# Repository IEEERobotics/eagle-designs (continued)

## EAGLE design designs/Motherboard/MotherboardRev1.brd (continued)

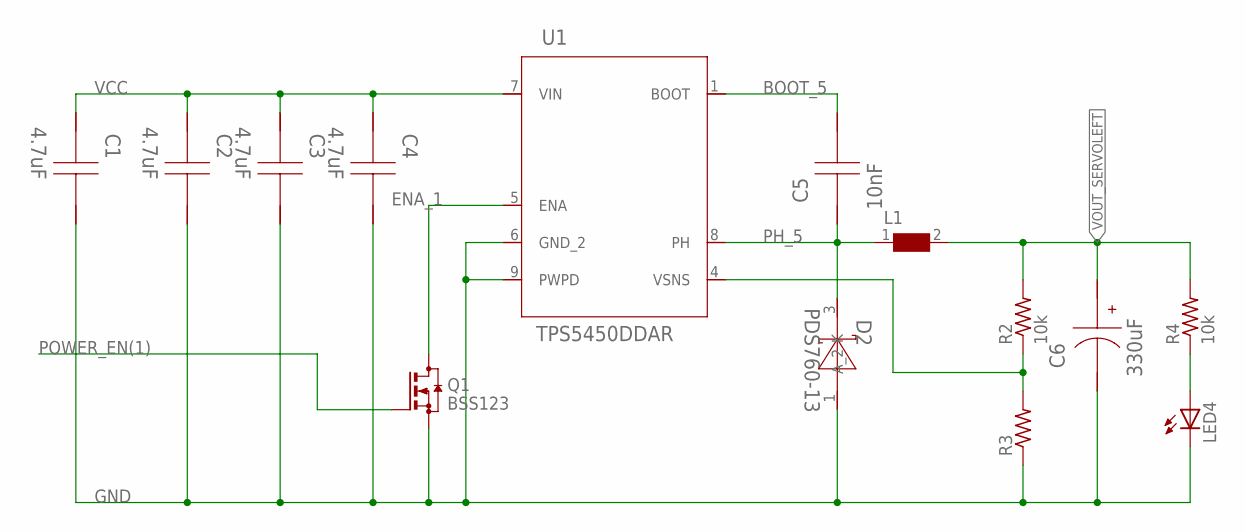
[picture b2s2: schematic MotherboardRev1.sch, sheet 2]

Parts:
C1, C2, C3, C4: 4.7uF; 1206
C5: 10nF; 0805
C6: 330uF; SM_RADIAL_10AMM
D2: PDS760-13; POWERDI5
L1: WE-HCC-7443331000_1090; WE-HCC_1090
LED4: LEDSML1206; SML1206
Q1: BSS123; SOT23
R2, R4: 10k; R1206
R3: R-US_R1206; R1206
U1: TPS5450DDAR; R-PDSO-G8

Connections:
BOOT_5: C5.1, U1.1 (BOOT); also elsewhere on the board
ENA_1: Q1.3 (D), U1.5 (ENA)
GND: C1.1, C2.1, C3.1, C4.1, C6.2 (-), D2.1 (A_2), LED4.C, Q1.2 (S), R3.1, U1.6 (GND_2), U1.9 (PWPD); also elsewhere on the board
unnamed: LED4.A, R4.1
PH_5: C5.2, D2.3 (K), L1.1, U1.8 (PH); also elsewhere on the board
POWER_EN(1): Q1.1 (G)
VCC: C1.2, C2.2, C3.2, C4.2, U1.7 (VIN); also elsewhere on the board
VOUT_SERVOLEFT: C6.1 (+), L1.2, R2.2, R4.2; also elsewhere on the board
VSNS_5: R2.1, R3.2, U1.4 (VSNS)

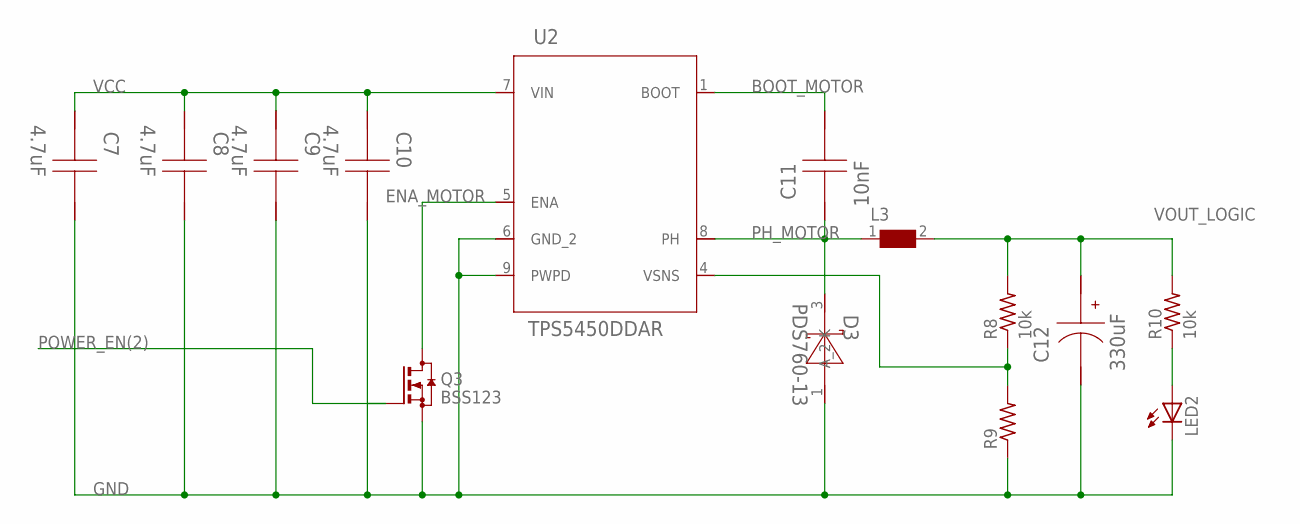
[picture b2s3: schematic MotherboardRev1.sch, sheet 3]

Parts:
C7, C8, C9, C10: 4.7uF; 1206
C11: 10nF; 0805
C12: 330uF; SM_RADIAL_10AMM
D3: PDS760-13; POWERDI5
L3: WE-HCC-7443331000_1090; WE-HCC_1090
LED2: LEDSML1206; SML1206
Q3: BSS123; SOT23
R8, R10: 10k; R1206
R9: R-US_R1206; R1206
U2: TPS5450DDAR; R-PDSO-G8

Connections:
BOOT_MOTOR: C11.1, U2.1 (BOOT); also elsewhere on the board
ENA_MOTOR: Q3.3 (D), U2.5 (ENA); also elsewhere on the board
GND: C7.1, C8.1, C9.1, C10.1, C12.2 (-), D3.1 (A_2), LED2.C, Q3.2 (S), R9.1, U2.6 (GND_2), U2.9 (PWPD); also elsewhere on the board
unnamed: LED2.A, R10.1
PH_MOTOR: C11.2, D3.3 (K), L3.1, U2.8 (PH); also elsewhere on the board
POWER_EN(2): Q3.1 (G)
VCC: C7.2, C8.2, C9.2, C10.2, U2.7 (VIN); also elsewhere on the board
VOUT_LOGIC: C12.1 (+), L3.2, R8.2, R10.2
VSNS1_MOTOR: R8.1, R9.2, U2.4 (VSNS)

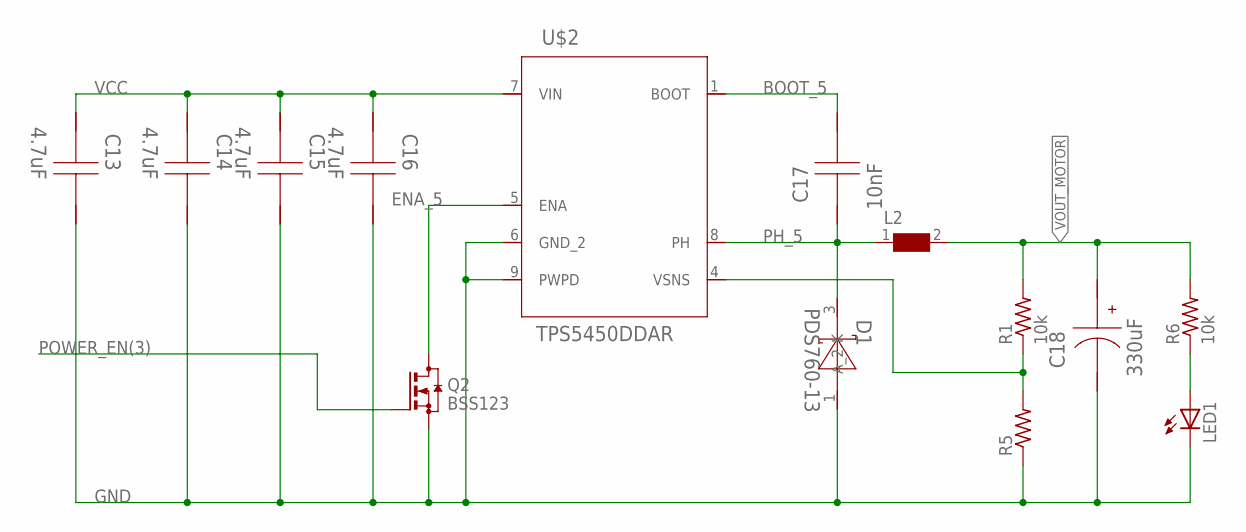
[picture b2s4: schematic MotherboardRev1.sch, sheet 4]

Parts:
C13, C14, C15, C16: 4.7uF; 1206
C17: 10nF; 0805
C18: 330uF; SM_RADIAL_10AMM
D1: PDS760-13; POWERDI5
L2: WE-HCC-7443331000_1090; WE-HCC_1090
LED1: LEDSML1206; SML1206
Q2: BSS123; SOT23
R1, R6: 10k; R1206
R5: R-US_R1206; R1206
U$2: TPS5450DDAR; R-PDSO-G8

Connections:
BOOT_5: C17.1, U$2.1 (BOOT); also elsewhere on the board
ENA_5: Q2.3 (D), U$2.5 (ENA)
GND: C13.1, C14.1, C15.1, C16.1, C18.2 (-), D1.1 (A_2), LED1.C, Q2.2 (S), R5.1, U$2.6 (GND_2), U$2.9 (PWPD); also elsewhere on the board
unnamed: LED1.A, R6.1
PH_5: C17.2, D1.3 (K), L2.1, U$2.8 (PH); also elsewhere on the board
POWER_EN(3): Q2.1 (G)
VCC: C13.2, C14.2, C15.2, C16.2, U$2.7 (VIN); also elsewhere on the board
VOUT_MOTOR: C18.1 (+), L2.2, R1.2, R6.2; also elsewhere on the board
VSNS_1: R1.1, R5.2, U$2.4 (VSNS)

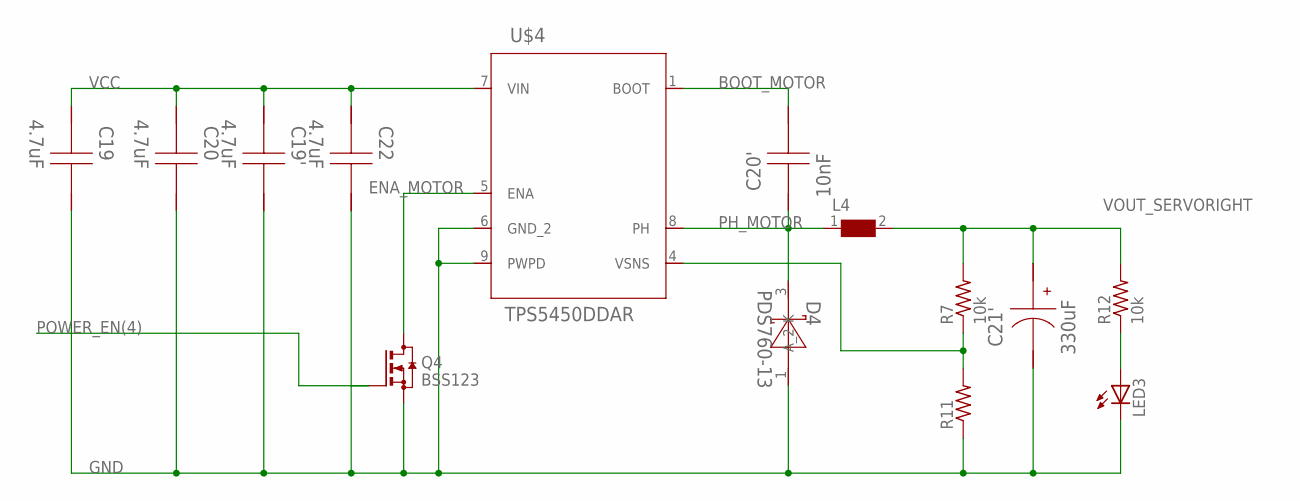
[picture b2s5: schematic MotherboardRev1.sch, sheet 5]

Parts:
C19, C19', C20, C22: 4.7uF; 1206
C20': 10nF; 0805
C21': 330uF; SM_RADIAL_10AMM
D4: PDS760-13; POWERDI5
L4: WE-HCC-7443331000_1090; WE-HCC_1090
LED3: LEDSML1206; SML1206
Q4: BSS123; SOT23
R7, R12: 10k; R1206
R11: R-US_R1206; R1206
U$4: TPS5450DDAR; R-PDSO-G8

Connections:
BOOT_MOTOR: C20'.1, U$4.1 (BOOT); also elsewhere on the board
ENA_MOTOR: Q4.3 (D), U$4.5 (ENA); also elsewhere on the board
GND: C19.1, C19'.1, C20.1, C21'.2 (-), C22.1, D4.1 (A_2), LED3.C, Q4.2 (S), R11.1, U$4.6 (GND_2), U$4.9 (PWPD); also elsewhere on the board
unnamed: LED3.A, R12.1
PH_MOTOR: C20'.2, D4.3 (K), L4.1, U$4.8 (PH); also elsewhere on the board
POWER_EN(4): Q4.1 (G)
VCC: C19.2, C19'.2, C20.2, C22.2, U$4.7 (VIN); also elsewhere on the board
VOUT_SERVORIGHT: C21'.1 (+), L4.2, R7.2, R12.2; also elsewhere on the board
VSNS1_MOTOR1: R7.1, R11.2, U$4.4 (VSNS)

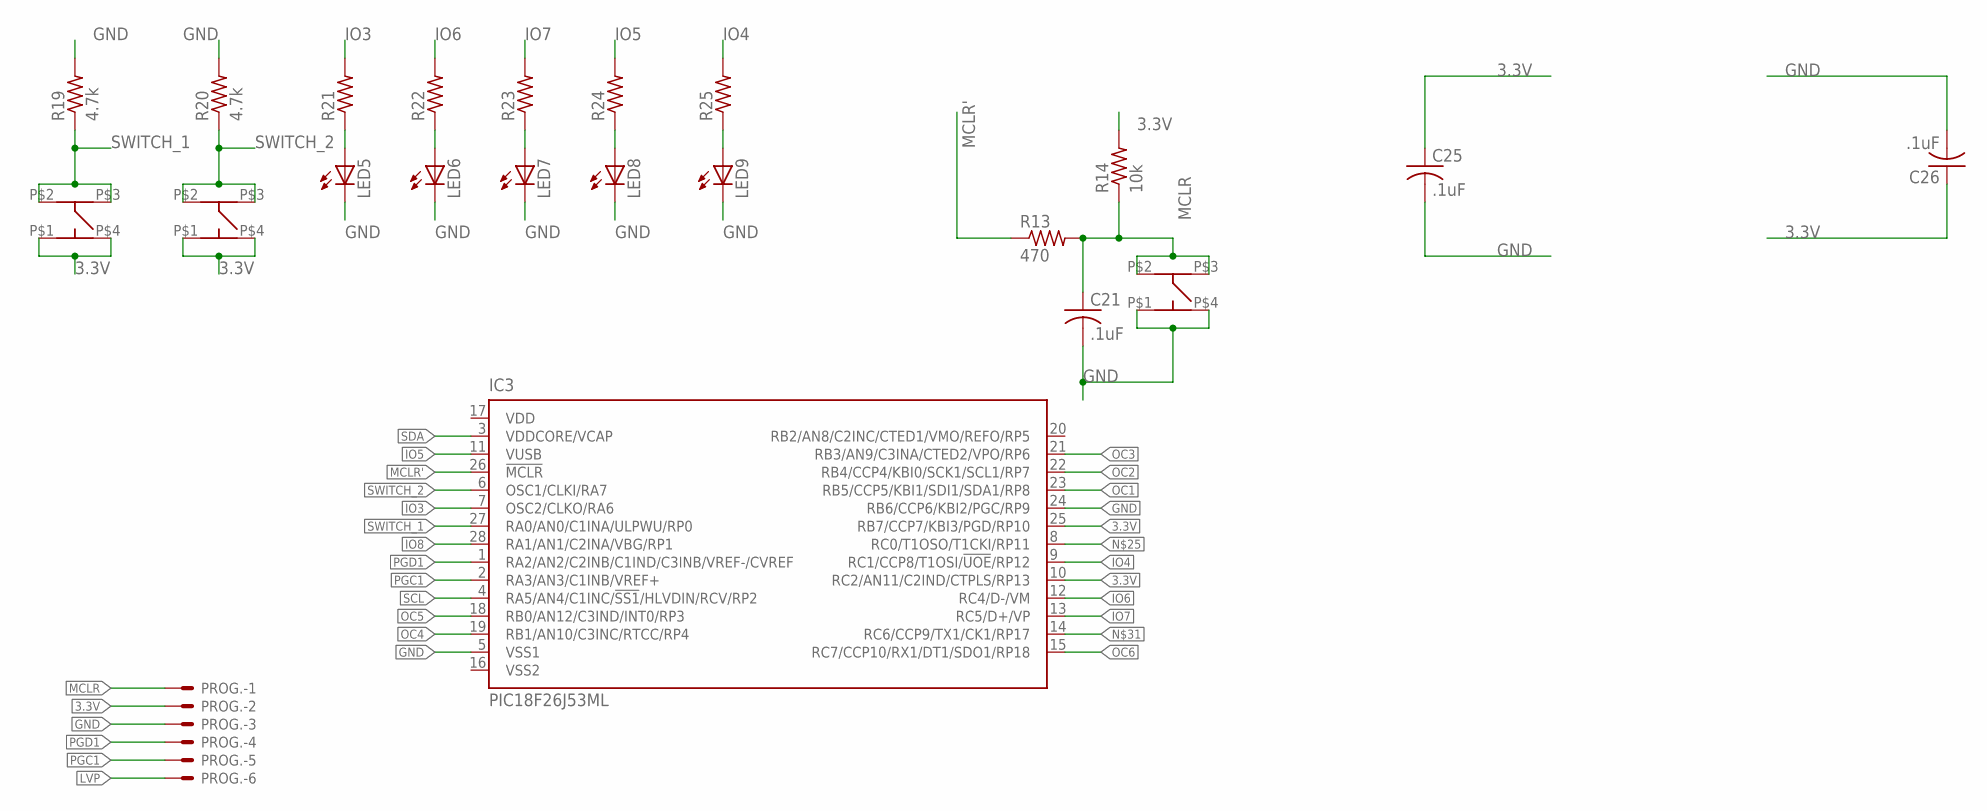
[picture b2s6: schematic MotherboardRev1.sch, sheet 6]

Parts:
C21, C25, C26: .1uF; C0805
IC3: PIC18F26J53ML; QFN28-ML_6X6MM
LED5, LED6, LED7, LED8, LED9: LED_LEDCHIPLED_1206; LED_CHIPLED_1206
PROG.: 22-23-2061
R13: 470; R0805
R14: 10k; R0805
R19, R20: 4.7k; R0805
R21, R22, R23, R24, R25: R-US_M0805; M0805
U$5: Switch3; MC32882_FINAL
U$6: Switch1; MC32882_FINAL
U$7: Switch2; MC32882_FINAL

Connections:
3.3V: C25.1, C26.1, IC3.10 (RC2/AN11/C2IND/CTPLS/RP13), IC3.25 (RB7/CCP7/KBI3/PGD/RP10), PROG..2, R14.2, U$6.P$1 (P1), U$6.P$4 (P4), U$7.P$1 (P1), U$7.P$4 (P4); also elsewhere on the board
GND: C21.2, C25.2, C26.2, IC3.5 (VSS1), IC3.24 (RB6/CCP6/KBI2/PGC/RP9), LED5.C, LED6.C, LED7.C, LED8.C, LED9.C, PROG..3, R19.2, R20.2, U$5.P$1 (P1), U$5.P$4 (P4); also elsewhere on the board
IO3: IC3.7 (OSC2/CLKO/RA6), R21.2
IO4: IC3.9 (RC1/CCP8/T1OSI/!UOE!/RP12), R25.2
IO5: IC3.11 (VUSB), R24.2
IO6: IC3.12 (RC4/D-/VM), R22.2
IO7: IC3.13 (RC5/D+/VP), R23.2
IO8: IC3.28 (RA1/AN1/C2INA/VBG/RP1)
LVP: PROG..6
MCLR: C21.1, PROG..1, R13.2, R14.1, U$5.P$2 (P2), U$5.P$3 (P3)
MCLR': IC3.26 (!MCLR), R13.1
unnamed: LED5.A, R21.1
unnamed: LED6.A, R22.1
unnamed: LED7.A, R23.1
unnamed: LED8.A, R24.1
unnamed: LED9.A, R25.1
OC1: IC3.23 (RB5/CCP5/KBI1/SDI1/SDA1/RP8); also elsewhere on the board
OC2: IC3.22 (RB4/CCP4/KBI0/SCK1/SCL1/RP7); also elsewhere on the board
OC3: IC3.21 (RB3/AN9/C3INA/CTED2/VPO/RP6); also elsewhere on the board
OC4: IC3.19 (RB1/AN10/C3INC/RTCC/RP4); also elsewhere on the board
OC5: IC3.18 (RB0/AN12/C3IND/INT0/RP3); also elsewhere on the board
OC6: IC3.15 (RC7/CCP10/RX1/DT1/SDO1/RP18); also elsewhere on the board
PGC1: IC3.2 (RA3/AN3/C1INB/VREF+), PROG..5
PGD1: IC3.1 (RA2/AN2/C2INB/C1IND/C3INB/VREF-/CVREF), PROG..4
SCL: IC3.4 (RA5/AN4/C1INC/!SS1!/HLVDIN/RCV/RP2); also elsewhere on the board
SDA: IC3.3 (VDDCORE/VCAP); also elsewhere on the board
SWITCH_1: IC3.27 (RA0/AN0/C1INA/ULPWU/RP0), R19.1, U$6.P$2 (P2), U$6.P$3 (P3)
SWITCH_2: IC3.6 (OSC1/CLKI/RA7), R20.1, U$7.P$2 (P2), U$7.P$3 (P3)

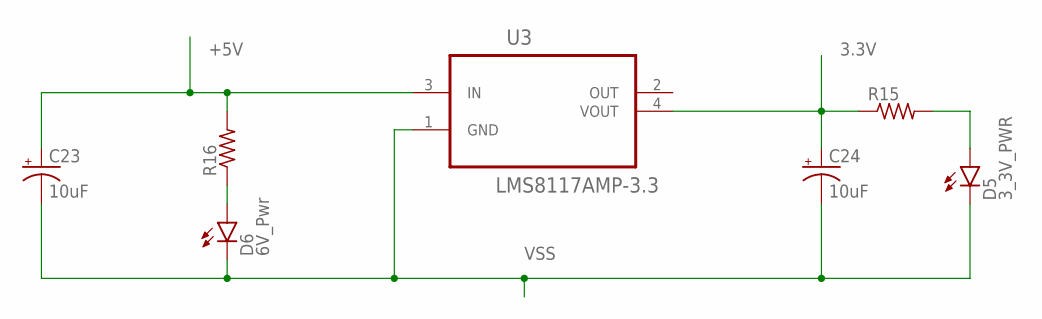
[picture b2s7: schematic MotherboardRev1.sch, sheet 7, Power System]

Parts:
C23, C24: 10uF; EIA3216
D5: 3_3V_PWR; FKIT-LED-1206
D6: 6V_Pwr; FKIT-LED-1206
R15, R16: R-US_R0805W; R0805W
U3: LMS8117AMP-3.3; SOT230P696X180-4N

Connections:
3.3V: C24.A (+), R15.1, U3.4 (VOUT); also elsewhere on the board
+5V: C23.A (+), R16.2, U3.3 (IN)
unnamed: D5.A, R15.2
unnamed: D6.A, R16.1
VSS: C23.C (-), C24.C (-), D5.C, D6.C, U3.1 (GND); also elsewhere on the board

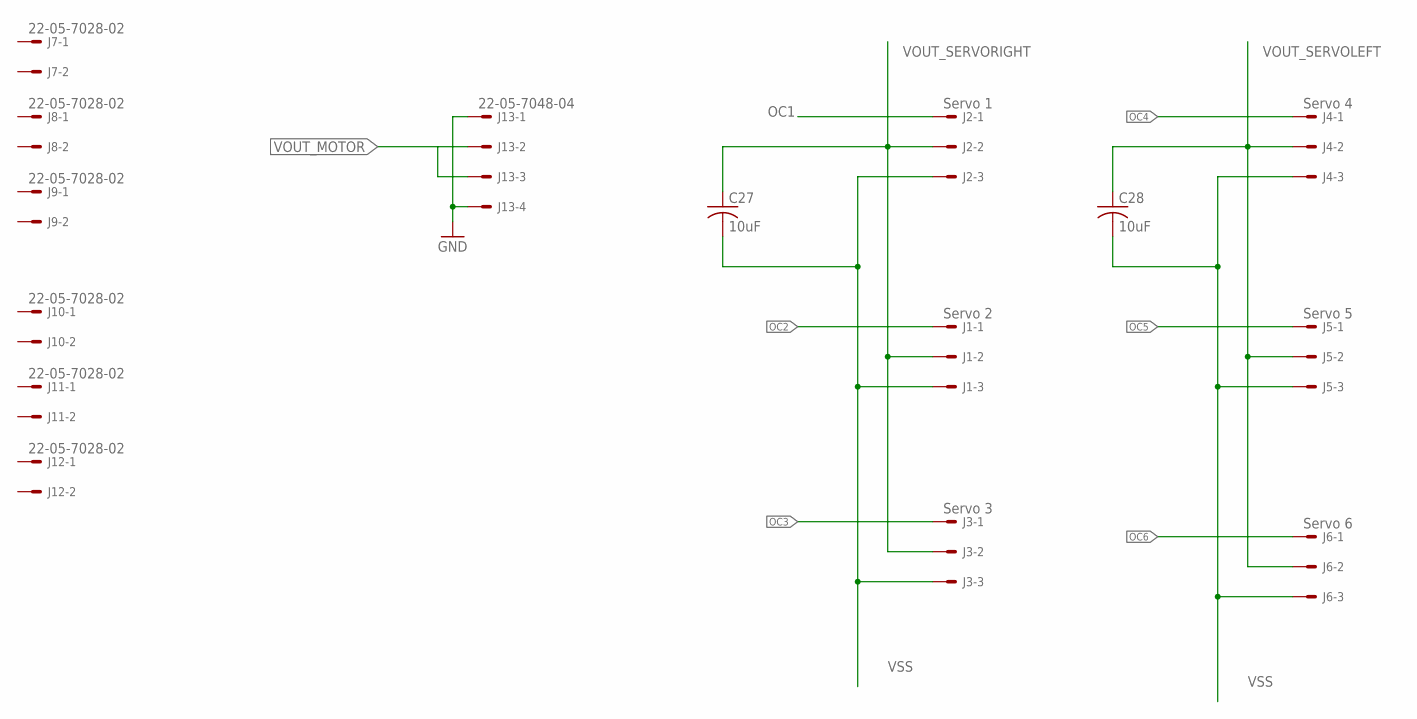
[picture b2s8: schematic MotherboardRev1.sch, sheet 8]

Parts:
C27, C28: 10uF; C0805
J1: Servo 2; 7395-03
J2: Servo 1; 7395-03
J3: Servo 3; 7395-03
J4: Servo 4; 7395-03
J5: Servo 5; 7395-03
J6: Servo 6; 7395-03
J7, J8, J9, J10, J11, J12: 22-05-7028-02; 7395-02
J13: 22-05-7048-04; 7395-04

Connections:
GND: J13.1, J13.4; also elsewhere on the board
OC1: J2.1; also elsewhere on the board
OC2: J1.1; also elsewhere on the board
OC3: J3.1; also elsewhere on the board
OC4: J4.1; also elsewhere on the board
OC5: J5.1; also elsewhere on the board
OC6: J6.1; also elsewhere on the board
VOUT_MOTOR: J13.2, J13.3; also elsewhere on the board
VOUT_SERVOLEFT: C28.1, J4.2, J5.2, J6.2; also elsewhere on the board
VOUT_SERVORIGHT: C27.1, J1.2, J2.2, J3.2; also elsewhere on the board
VSS: C27.2, C28.2, J1.3, J2.3, J3.3, J4.3, J5.3, J6.3; also elsewhere on the board

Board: 2 copper layers, 101 parts (32 on the bottom side), 50 nets, no tracks yet.

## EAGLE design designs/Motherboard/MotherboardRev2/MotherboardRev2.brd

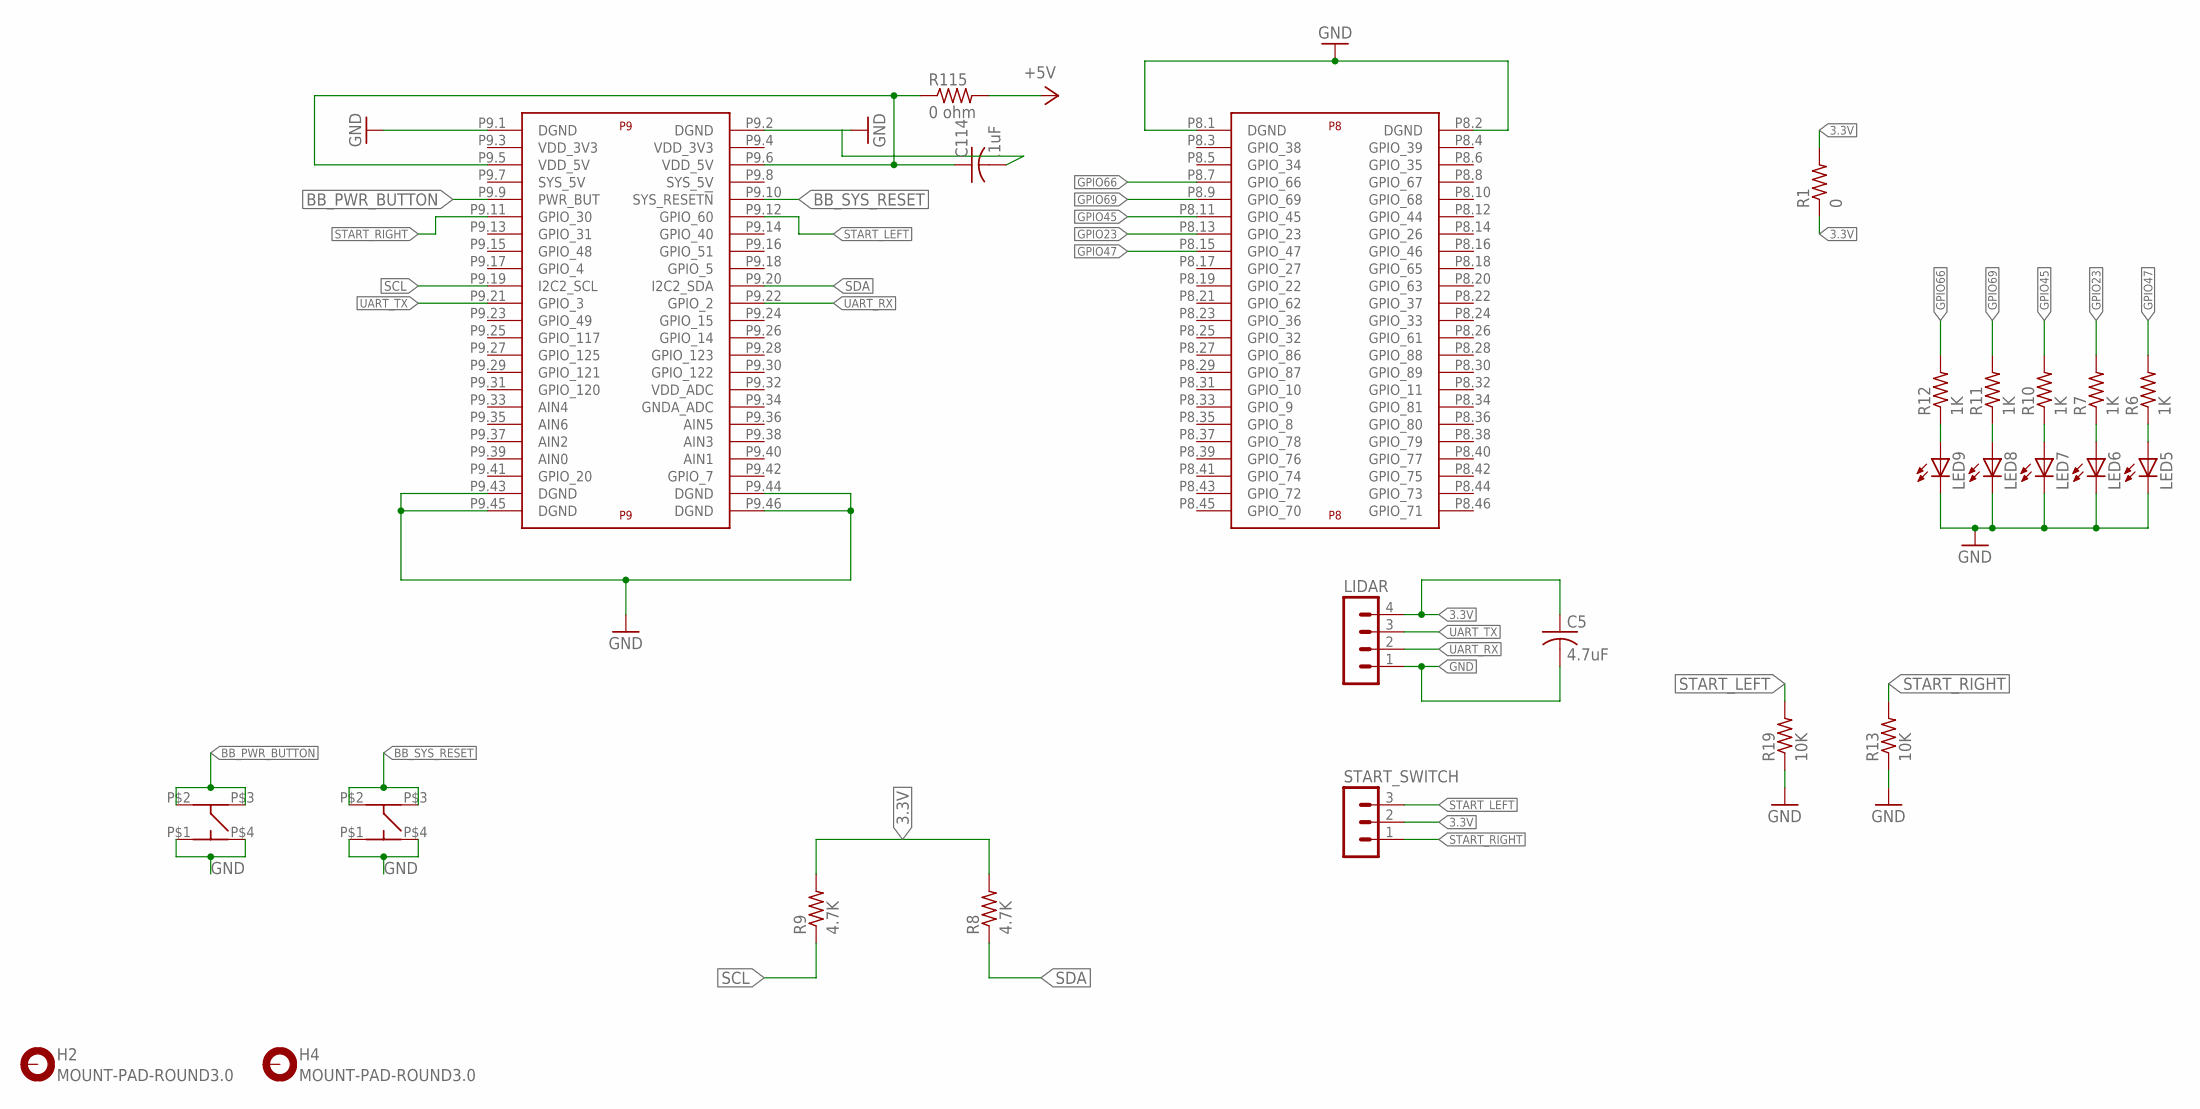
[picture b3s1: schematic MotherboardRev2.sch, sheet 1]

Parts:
C5: 4.7uF; C0402
C114: .1uF; C0402
H2, H4: MOUNT-PAD-ROUND3.0; 3,0-PAD
LED5, LED6, LED7, LED8, LED9: LEDCHIP-LED0603; CHIP-LED0603
LIDAR: MA04-1
R1: 0; R0805
R6, R7, R10, R11, R12: 1K; R0402
R8, R9: 4.7K; R0402
R13, R19: 10K; R0402
R115: 0 ohm; R0805
START_SWITCH: MA03-1
U$5: BEAGLE_BONE_BLACK_CAPE
U$100, U$101: Switch1; MC32882_FINAL

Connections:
3.3V: C5.1, LIDAR.4, R1.1, R1.2, R8.2, R9.2, START_SWITCH.2; also elsewhere on the board
BB_PWR_BUTTON: U$5.P9.9 (PWR_BUT), U$101.P$2 (P2), U$101.P$3 (P3)
BB_SYS_RESET: U$5.P9.10 (SYS_RESET!N), U$100.P$2 (P2), U$100.P$3 (P3)
GND: C5.2, C114.2, LED5.C, LED6.C, LED7.C, LED8.C, LED9.C, LIDAR.1, R13.1, R19.1, U$5.P8.1 (DGND), U$5.P8.2 (DGND), U$5.P9.1 (DGND), U$5.P9.2 (DGND), U$5.P9.43 (DGND), U$5.P9.44 (DGND), U$5.P9.45 (DGND), U$5.P9.46 (DGND), U$100.P$1 (P1), U$100.P$4 (P4), U$101.P$1 (P1), U$101.P$4 (P4); also elsewhere on the board
GPIO23: R7.2, U$5.P8.13 (GPIO_23)
GPIO45: R10.2, U$5.P8.11 (GPIO_45)
GPIO47: R6.2, U$5.P8.15 (GPIO_47)
GPIO66: R12.2, U$5.P8.7 (GPIO_66)
GPIO69: R11.2, U$5.P8.9 (GPIO_69)
unnamed: C114.1, R115.1, U$5.P9.5 (VDD_5V), U$5.P9.6 (VDD_5V)
unnamed: LED9.A, R12.1
unnamed: LED8.A, R11.1
unnamed: LED7.A, R10.1
unnamed: LED6.A, R7.1
unnamed: LED5.A, R6.1
SCL: R9.1, U$5.P9.19 (I2C2_SCL); also elsewhere on the board
SDA: R8.1, U$5.P9.20 (I2C2_SDA); also elsewhere on the board
START_LEFT: R19.2, START_SWITCH.3, U$5.P9.12 (GPIO_60)
START_RIGHT: R13.2, START_SWITCH.1, U$5.P9.11 (GPIO_30)
UART_RX: LIDAR.2, U$5.P9.22 (GPIO_2)
UART_TX: LIDAR.3, U$5.P9.21 (GPIO_3)
VOUT1: R115.2; also elsewhere on the board

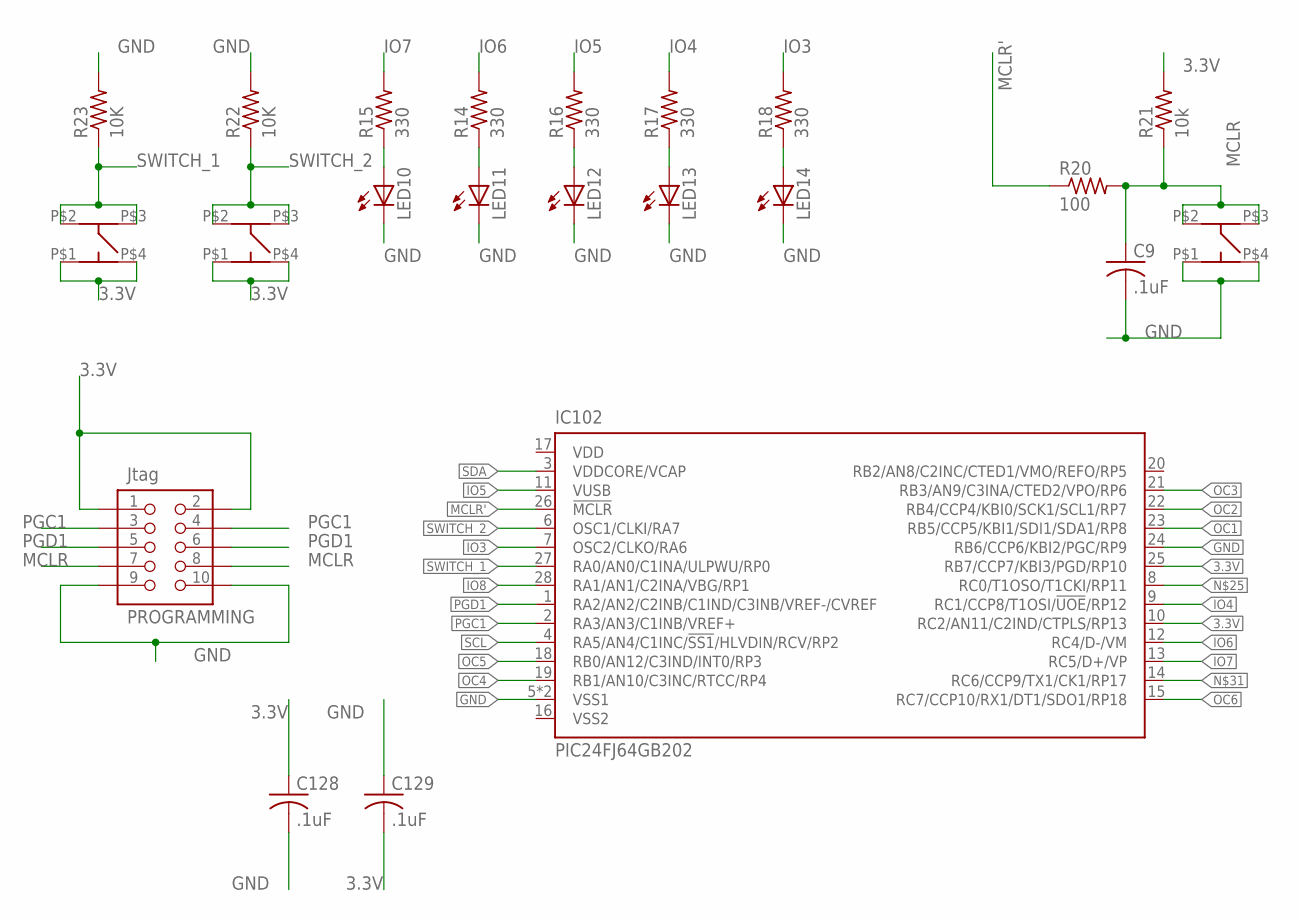
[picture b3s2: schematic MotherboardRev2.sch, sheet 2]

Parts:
C9, C128, C129: .1uF; C0402
IC102: PIC24FJ64GB202; QFN28-ML_6X6MM
LED10, LED11, LED12, LED13, LED14: LEDCHIP-LED0603; CHIP-LED0603
PROGRAMMING: Jtag; MOTHER-BOARD-REV5_10-PIN-SMD
R14, R15, R16, R17, R18: 330; R0402
R20: 100; R0402
R21: 10k; R0402
R22, R23: 10K; R0402
U$3: Switch2; MC32882_FINAL
U$4: Switch1; MC32882_FINAL
U$102: Switch3; MC32882_FINAL

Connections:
3.3V: C128.1, C129.1, IC102.10 (RC2/AN11/C2IND/CTPLS/RP13), IC102.25 (RB7/CCP7/KBI3/PGD/RP10), PROGRAMMING.1, PROGRAMMING.2, R21.2, U$3.P$1 (P1), U$3.P$4 (P4), U$4.P$1 (P1), U$4.P$4 (P4); also elsewhere on the board
GND: C9.2, C128.2, C129.2, IC102.5 (VSS1), IC102.24 (RB6/CCP6/KBI2/PGC/RP9), IC102.EXP (VSS1), LED10.C, LED11.C, LED12.C, LED13.C, LED14.C, PROGRAMMING.9, PROGRAMMING.10, R22.2, R23.2, U$102.P$1 (P1), U$102.P$4 (P4); also elsewhere on the board
IO3: IC102.7 (OSC2/CLKO/RA6), R18.2
IO4: IC102.9 (RC1/CCP8/T1OSI/!UOE!/RP12), R17.2
IO5: IC102.11 (VUSB), R16.2
IO6: IC102.12 (RC4/D-/VM), R14.2
IO7: IC102.13 (RC5/D+/VP), R15.2
IO8: IC102.28 (RA1/AN1/C2INA/VBG/RP1)
MCLR: C9.1, PROGRAMMING.7, PROGRAMMING.8, R20.2, R21.1, U$102.P$2 (P2), U$102.P$3 (P3)
MCLR': IC102.26 (!MCLR), R20.1
unnamed: LED10.A, R15.1
unnamed: LED11.A, R14.1
unnamed: LED12.A, R16.1
unnamed: LED13.A, R17.1
unnamed: LED14.A, R18.1
OC1: IC102.23 (RB5/CCP5/KBI1/SDI1/SDA1/RP8); also elsewhere on the board
OC2: IC102.22 (RB4/CCP4/KBI0/SCK1/SCL1/RP7); also elsewhere on the board
OC3: IC102.21 (RB3/AN9/C3INA/CTED2/VPO/RP6); also elsewhere on the board
OC4: IC102.19 (RB1/AN10/C3INC/RTCC/RP4); also elsewhere on the board
OC5: IC102.18 (RB0/AN12/C3IND/INT0/RP3); also elsewhere on the board
OC6: IC102.15 (RC7/CCP10/RX1/DT1/SDO1/RP18); also elsewhere on the board
PGC1: IC102.2 (RA3/AN3/C1INB/VREF+), PROGRAMMING.3, PROGRAMMING.4
PGD1: IC102.1 (RA2/AN2/C2INB/C1IND/C3INB/VREF-/CVREF), PROGRAMMING.5, PROGRAMMING.6
SCL: IC102.4 (RA5/AN4/C1INC/!SS1!/HLVDIN/RCV/RP2); also elsewhere on the board
SDA: IC102.3 (VDDCORE/VCAP); also elsewhere on the board
SWITCH_1: IC102.27 (RA0/AN0/C1INA/ULPWU/RP0), R23.1, U$4.P$2 (P2), U$4.P$3 (P3)
SWITCH_2: IC102.6 (OSC1/CLKI/RA7), R22.1, U$3.P$2 (P2), U$3.P$3 (P3)

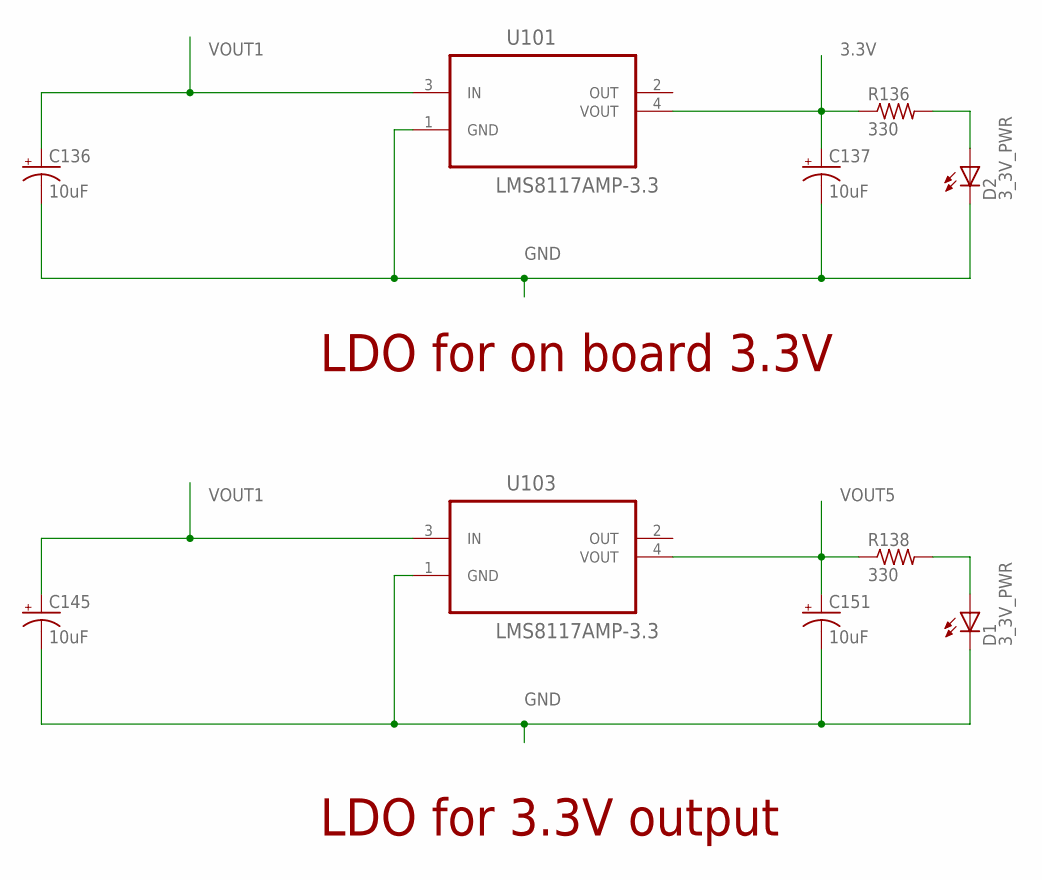
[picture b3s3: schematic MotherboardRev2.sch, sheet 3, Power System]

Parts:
C136, C137, C145, C151: 10uF; EIA3216
D1, D2: 3_3V_PWR; CHIP-LED0603
R136, R138: 330; R0402
U101, U103: LMS8117AMP-3.3; SOT230P696X180-4N

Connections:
3.3V: C137.A (+), R136.1, U101.4 (VOUT); also elsewhere on the board
GND: C136.C (-), C137.C (-), C145.C (-), C151.C (-), D1.C, D2.C, U101.1 (GND), U103.1 (GND); also elsewhere on the board
unnamed: D2.A, R136.2
unnamed: D1.A, R138.2
VOUT1: C136.A (+), C145.A (+), U101.3 (IN), U103.3 (IN); also elsewhere on the board
VOUT5: C151.A (+), R138.1, U103.4 (VOUT); also elsewhere on the board

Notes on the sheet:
LDO for on board 3.3V
LDO for 3.3V output

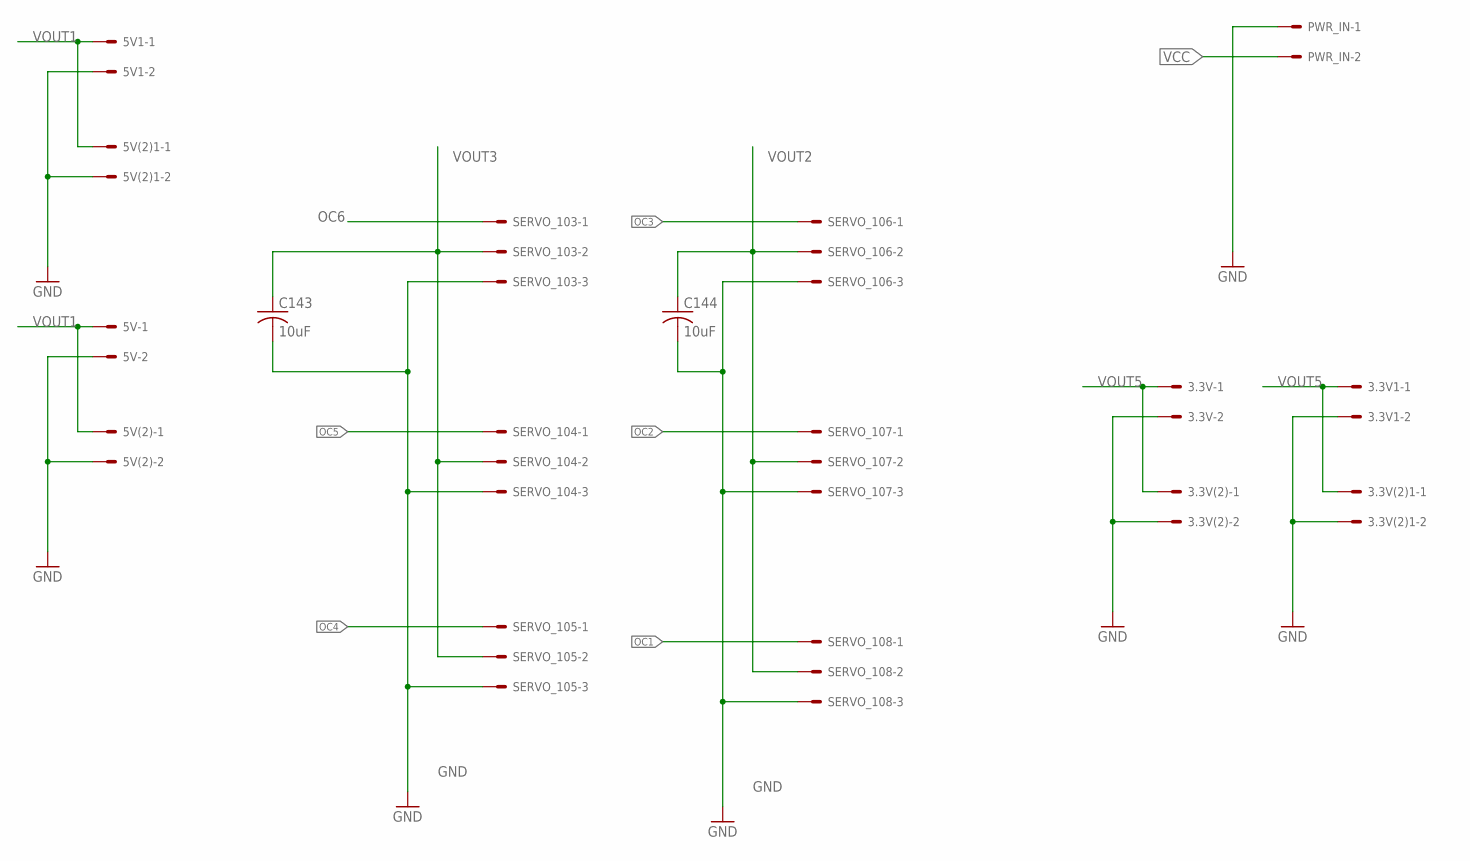
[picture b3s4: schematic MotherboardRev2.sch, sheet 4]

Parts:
3.3V, 3.3V1, 3.3V(2), 3.3V(2)1, 5V, 5V1, 5V(2), 5V(2)1: 22-05-7028-02; 7395-02
C143, C144: 10uF; C0805
PWR_IN: 555X-2H; 5569-2
SERVO_103, SERVO_104, SERVO_105, SERVO_106, SERVO_107, SERVO_108: 22-05-7038-03; 7395-03

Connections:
GND: 3.3V.2, 3.3V1.2, 3.3V(2).2, 3.3V(2)1.2, 5V.2, 5V1.2, 5V(2).2, 5V(2)1.2, C143.2, C144.2, PWR_IN.1, SERVO_103.3, SERVO_104.3, SERVO_105.3, SERVO_106.3, SERVO_107.3, SERVO_108.3; also elsewhere on the board
OC1: SERVO_108.1; also elsewhere on the board
OC2: SERVO_107.1; also elsewhere on the board
OC3: SERVO_106.1; also elsewhere on the board
OC4: SERVO_105.1; also elsewhere on the board
OC5: SERVO_104.1; also elsewhere on the board
OC6: SERVO_103.1; also elsewhere on the board
VCC: PWR_IN.2; also elsewhere on the board
VOUT1: 5V.1, 5V1.1, 5V(2).1, 5V(2)1.1; also elsewhere on the board
VOUT2: C144.1, SERVO_106.2, SERVO_107.2, SERVO_108.2; also elsewhere on the board
VOUT3: C143.1, SERVO_103.2, SERVO_104.2, SERVO_105.2; also elsewhere on the board
VOUT5: 3.3V.1, 3.3V1.1, 3.3V(2).1, 3.3V(2)1.1; also elsewhere on the board

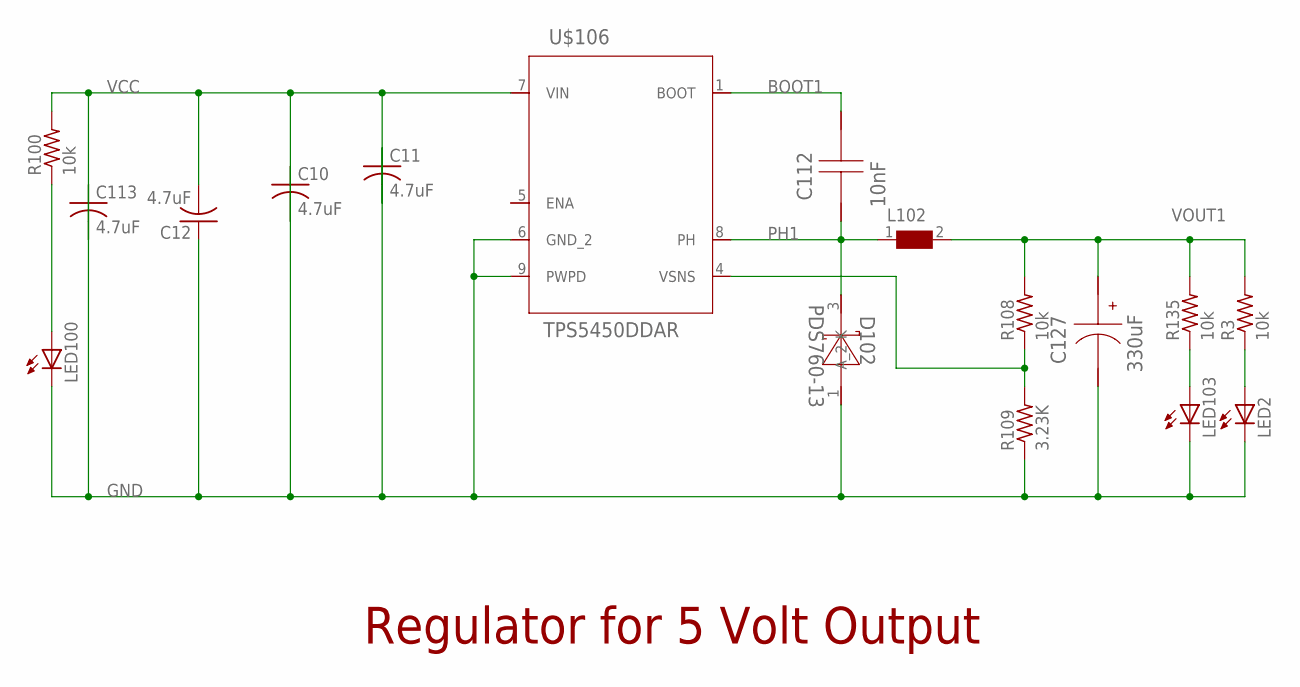
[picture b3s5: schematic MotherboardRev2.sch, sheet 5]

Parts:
C10, C11, C12, C113: 4.7uF; C0805
C112: 10nF; 0805
C127: 330uF; SM_RADIAL_10AMM
D102: PDS760-13; POWERDI5
L102: WE-HCC-7443331000_1090; WE-HCC_1090
LED2, LED100, LED103: LEDCHIP-LED0603; CHIP-LED0603
R3, R100, R108, R135: 10k; R0402
R109: 3.23K; R0402
U$106: TPS5450DDAR; R-PDSO-G8

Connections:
BOOT1: C112.1, U$106.1 (BOOT)
GND: C10.1, C11.1, C12.1, C113.1, C127.2 (-), D102.1 (A_2), LED2.C, LED100.C, LED103.C, R109.1, U$106.6 (GND_2), U$106.9 (PWPD); also elsewhere on the board
unnamed: LED103.A, R135.1
unnamed: LED100.A, R100.1
unnamed: LED2.A, R3.1
PH1: C112.2, D102.3 (K), L102.1, U$106.8 (PH)
VCC: C10.2, C11.2, C12.2, C113.2, R100.2, U$106.7 (VIN); also elsewhere on the board
VOUT1: C127.1 (+), L102.2, R3.2, R108.2, R135.2; also elsewhere on the board
VSNS1: R108.1, R109.2, U$106.4 (VSNS)

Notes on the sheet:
Regulator for 5 Volt Output

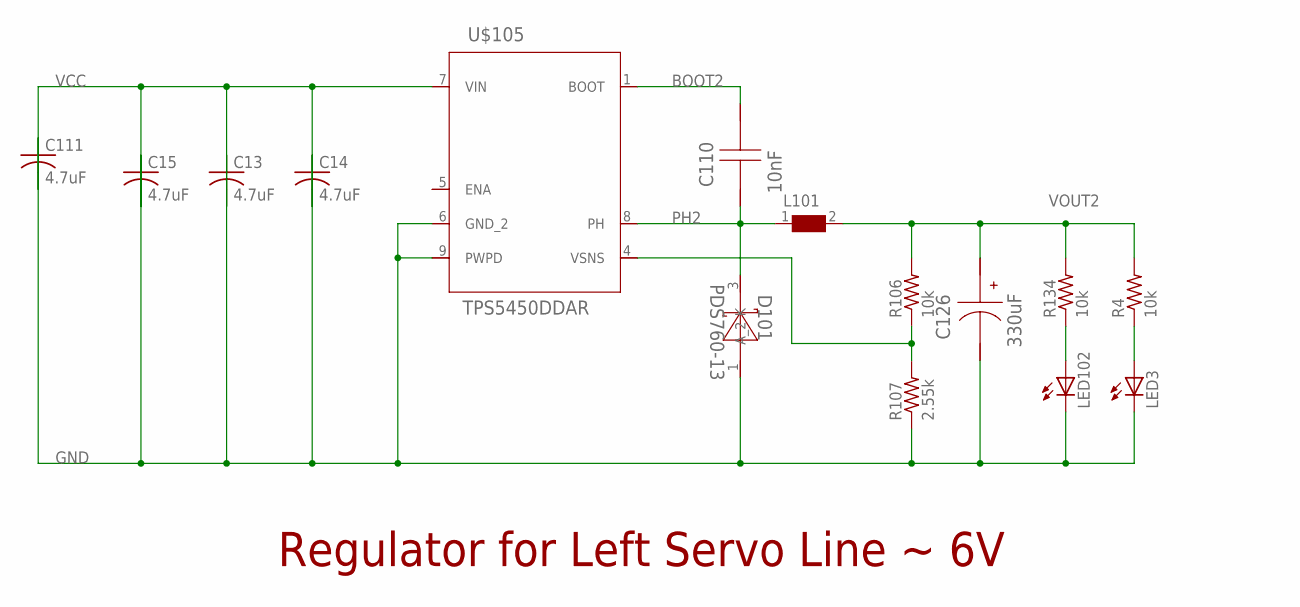
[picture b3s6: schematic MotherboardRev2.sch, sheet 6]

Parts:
C13, C14, C15, C111: 4.7uF; C0805
C110: 10nF; 0805
C126: 330uF; SM_RADIAL_10AMM
D101: PDS760-13; POWERDI5
L101: WE-HCC-7443331000_1090; WE-HCC_1090
LED3, LED102: LEDCHIP-LED0603; CHIP-LED0603
R4, R106, R134: 10k; R0402
R107: 2.55k; R0402
U$105: TPS5450DDAR; R-PDSO-G8

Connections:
BOOT2: C110.1, U$105.1 (BOOT)
GND: C13.1, C14.1, C15.1, C111.1, C126.2 (-), D101.1 (A_2), LED3.C, LED102.C, R107.1, U$105.6 (GND_2), U$105.9 (PWPD); also elsewhere on the board
unnamed: LED102.A, R134.1
unnamed: LED3.A, R4.1
PH2: C110.2, D101.3 (K), L101.1, U$105.8 (PH)
VCC: C13.2, C14.2, C15.2, C111.2, U$105.7 (VIN); also elsewhere on the board
VOUT2: C126.1 (+), L101.2, R4.2, R106.2, R134.2; also elsewhere on the board
VSNS2: R106.1, R107.2, U$105.4 (VSNS)

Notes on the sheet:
Regulator for Left Servo Line ~ 6V

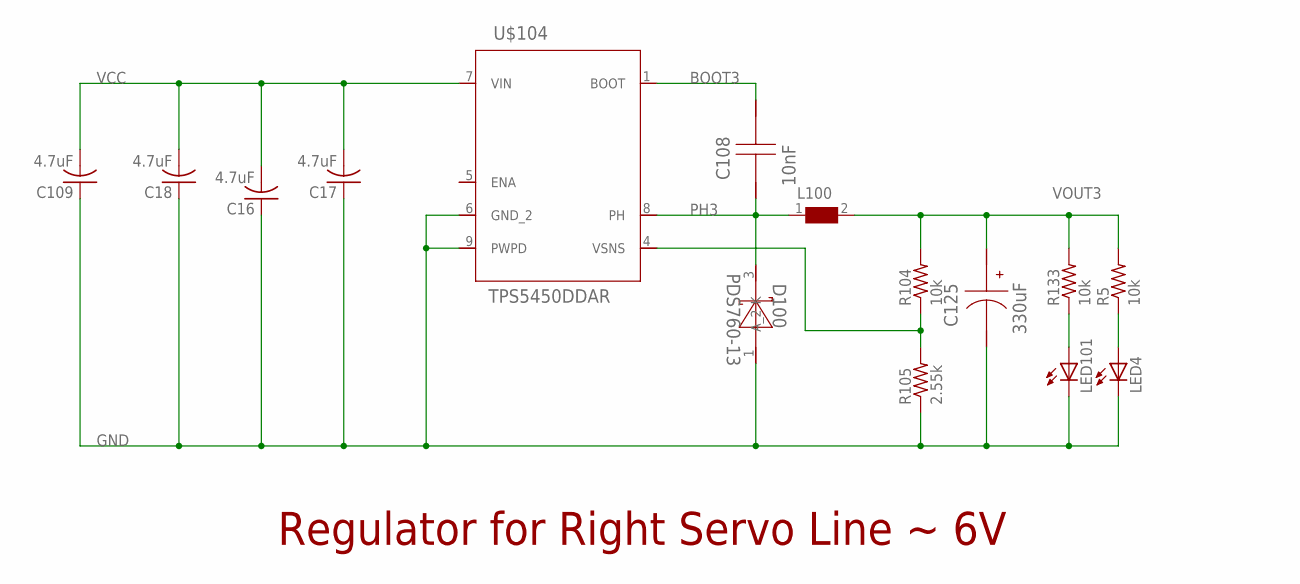
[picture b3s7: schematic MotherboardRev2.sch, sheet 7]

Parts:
C16, C17, C18, C109: 4.7uF; C0805
C108: 10nF; 0805
C125: 330uF; SM_RADIAL_10AMM
D100: PDS760-13; POWERDI5
L100: WE-HCC-7443331000_1090; WE-HCC_1090
LED4, LED101: LEDCHIP-LED0603; CHIP-LED0603
R5, R104, R133: 10k; R0402
R105: 2.55k; R0402
U$104: TPS5450DDAR; R-PDSO-G8

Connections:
BOOT3: C108.1, U$104.1 (BOOT)
GND: C16.1, C17.1, C18.1, C109.1, C125.2 (-), D100.1 (A_2), LED4.C, LED101.C, R105.1, U$104.6 (GND_2), U$104.9 (PWPD); also elsewhere on the board
unnamed: LED101.A, R133.1
unnamed: LED4.A, R5.1
PH3: C108.2, D100.3 (K), L100.1, U$104.8 (PH)
VCC: C16.2, C17.2, C18.2, C109.2, U$104.7 (VIN); also elsewhere on the board
VOUT3: C125.1 (+), L100.2, R5.2, R104.2, R133.2; also elsewhere on the board
VSNS3: R104.1, R105.2, U$104.4 (VSNS)

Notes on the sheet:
Regulator for Right Servo Line ~ 6V
